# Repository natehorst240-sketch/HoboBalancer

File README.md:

# HoboBalancer

Hobby helicopter rotor-balancing instrumentation. KiCad 10 projects plus ESP32-S3
firmware.

> **Reference and troubleshooting only.** These boards report approximate RPM, 1/rev
> vibration magnitude, phase, stability and trends. Maintenance balancing remains with
> calibrated MicroVib / DynaVibe equipment. Neither the firmware nor the physical
> measurement accuracy has been validated on a bench, let alone on an aircraft. Nothing
> here is airworthiness-approved.

Open the projects in **KiCad 10.0.3 or later**. They use the KiCad 10 file format and
KiCad 9 will not open them.

## Projects

| Directory | Board | Revision | State |
|---|---|---|---|
| `.` (root) | `Balancer` — STM32 balancer | Rev A | Schematic only; `Balancer.kicad_pcb` is an empty stub |
| `BalancerREF/` | **HOBOVibe** — ESP32-S3 reference puck | **Rev G** | 50 × 50 mm, 4 layer, fully routed, DRC clean apart from three accepted warnings (see below) |
| `BalancerREF_OptHead/` | Optical tach head | **Rev B** | 25 × 50 mm, 2 layer, routed; no mounting holes yet |

Both boards are routed. On the main board `SYS`, `SYS_SW`, `BAT` and `USB_VBUS` had been
routed across In2.Cu, which is the +3V3 plane; those tracks were removed on 2026-09-18 so
the plane is whole again, and those four nets were then re-routed on the outer layers (PR #7,
merged with Rev G on 2026-09-19). The Rev G connections (U7 pass-through, R39) are routed too.
`BalancerREF/review/drc-review.rpt` (KiCad 10.0.6) shows 0 errors and 0 unconnected; what is
left is the GCT USB-C footprint's own peg-to-pad spacing (4), the ESP32 antenna overhanging
the edge by design (2) and the locally edited U1 footprint (1).
Placement was machine-generated and then adjusted by hand; look at it in pcbnew before
trusting it.

Both carry pick-and-place **fiducials** (1 mm dot, 2 mm mask opening): three per
populated face, at three of the four corners. Never four — a symmetric set gives the
placement machine no way to tell a 180°-rotated panel from a correct one. The main
board has them on both faces; the optical head is single-sided so its back has none.

### Track widths

Net classes are set in each `.kicad_pro`, sized from IPC-2221 at 1 oz outer copper and
a 10 °C rise (0.20 mm ≈ 0.74 A, 0.50 mm ≈ 1.45 A, 0.80 mm ≈ 2.03 A):

| Class | Track | Nets |
|---|---|---|
| Default | 0.20 mm | everything else |
| Power | 0.50 mm | `+3V3` `SYS` `SYS_SW` `BAT` `USB_VBUS` `GND` |
| Switch | 0.80 mm | `U6-L1` `U6-L2` — main board only |
| USB | 0.20 mm | `D+`/`D-` both sides, diff pair 0.20/0.15 |
| Emitter | 0.80 mm | `SYS_SW` `D1-A` `D1-K` — head board only |

The emitter resistor is sized at the **top** of the SYS_SW range, not at the battery.
The BQ24075 regulates OUT to 5.5 V, so R18 is 3.9 Ω for about 0.49 A at a full cell and
about 0.90 A worst case — under D1's 1 A absolute maximum. At the old 3.0 Ω the USB case
reached roughly 1.1 A.

Two caveats. **Switch clearance stays at 0.20 mm**, not the 0.25 the wider track might
suggest: the TPS63031's WSON-10 places its own L1/L2 pads 0.20 mm from its thermal
pad, so anything stricter fails inside the package and no routing choice can fix it.
And the **USB numbers are not an impedance solution** — real 90 Ω differential needs
the fab's actual stackup. The ESP32-S3's native USB is Full Speed (12 Mbps), where
that matters far less than it would at High Speed.

### BalancerREF (HOBOVibe)

The main puck. ESP32-S3-MINI-1, IIS3DWB vibration sensor on SPI, LM1815 magnetic tach
front end, BQ24075 charger with an integrated dynamic power path, TPS63031 buck-boost, and a
1x05 header for an optional u-blox-class GPS used by the in-flight logging mode.

Two measurement profiles: **MR-VERT** uses an external isolated two-wire VR pickup;
**TR-VERT** uses the optical tach against retroreflective tape.

50 × 50 mm, four layers, components on both faces: ICs, connectors, switches and test
points on the front, passives on the back so each decoupling cap sits under its IC's
power pins. M2.5 mounting holes at the four corners, on a 43.40 × 42.90 mm rectangle
centred on the board. U1's antenna deliberately overhangs the top edge, which puts
almost all of its keepout off the board — the wide band still reaches 0.44 mm inside
the top edge, which is why the mounting-hole rectangle is 0.5 mm shorter than it is
wide. The overhang is required anyway, because the aluminium bracket must not sit
behind a PCB antenna.

The puck mounts **vertically, ESP32 to the left and USB-C to the right**. `UP` and
`LEFT` markers on the front silkscreen record that; with the board vertical the
accelerometer's vertical axis is in-plane (stiff) and the flexible out-of-plane axis
carries lateral instead. Which sensor channel that is still needs recording from
DS12569's orientation figure — firmware can also identify it at runtime, since the
vertical axis reads a static 1 g when the puck is mounted upright.

Three switches: SW1 power slide, SW2 acquire, SW3 boot. There is no reset button —
SW1 feeds U6's VIN and EN, so the power slide already power-cycles the MCU. SW1 is a
Würth WS-SLTV rated 300 mA switching; steady draw through it is about 180 mA, but BLE
TX bursts and switch-on inrush exceed that briefly. That is accepted as reduced switch
life rather than designed out — see DATASHEET-VERIFICATION.md.

**Sleep is not low power.** The LM1815 draws 3.6 mA typical (6 mA max) and sits on the
always-on 3V3 rail, as do the head's op-amp and comparator, so a sleeping puck draws
milliamps and a 500 mAh cell lasts days rather than months. If flight logging ever
depends on long sleeps, the fix is a load switch on the LM1815 and the head supply.

**Power path and charging.** A BQ24075 runs the input: it charges the cell and powers
the system from the same input independently, so charge termination is correct while
the puck is running, and it will run with a defective or absent pack. R3 (3.57 k)
sets fast charge to about 249 mA — 0.5C for a 500 mAh cell — and R35 (1.6 k) sets the
resistor-programmed input limit to about 1.0 A.

Four pins go to the MCU. `CHG_EN1` (GPIO5) and `CHG_EN2` (GPIO18) select the input
current limit; `PGOOD_N` (GPIO21) and `CHG_STAT` (GPIO38) are open-drain status inputs
with 100 k pull-ups, both **active low**. Two things are easy to get wrong here:

- The datasheet's current-limit table is indexed **(EN2, EN1)**, the reverse of the
  order the pins are named in.
- Both EN pins have 285 k internal pulldowns, so the limit is USB100 — **100 mA** —
  until firmware deliberately raises it.

`PGOOD_N` is the USB-present signal. Earlier revisions tried to infer that by comparing
two ADC dividers, because a single reading of `SYS_SW` cannot answer it: SYS was fed
either from USB through a Schottky or from the cell through a PFET, and the ranges
overlap. The BQ24075 arbitrates the input itself and simply reports the answer, so
Rev E deleted the second divider (`BAT_SENSE`, R33/R34/C31) along with its 500 k ADC
source impedance and its ~2 µA standing drain on the cell.

`SUPPLY_SENSE` (`SYS_SW/2` on GPIO12) survives as the supply-voltage reading. While the
puck runs unplugged the BQ24075 connects OUT to the battery, so it reads the cell; while
charging it reads the input-derived rail instead, not the cell. It is on ADC2_CH1, the
converter shared with the radio — worth knowing, because it is now the only supply
measurement on the board.

See [`BalancerREF/README.md`](BalancerREF/README.md) for the circuit description and
[`BalancerREF/DATASHEET-VERIFICATION.md`](BalancerREF/DATASHEET-VERIFICATION.md) for
every pin mapping checked against the manufacturer tables.

### BalancerREF_OptHead

The optical tach front end, split onto its own board on 2026-09-11. It mounts at 90° to
the main PCB on the second leg of an aluminium L-bracket, on a pivot bolt so the emitter
can be aimed at the tape. The split exists because neither optical part has leads to
form — the XPEBRD-L1 is a ceramic SMD LED and the BPW34S is the surface-mount BPW34 — so
they need their own copper.

The cut is deliberately placed **after** the comparator. The cable then carries only DC
rails and digital edges; cutting at the photodiode would have put the 10 kΩ
transimpedance summing junction on a flying lead beside a wire switching 500 mA at
20 kHz.

Connected to the main board by a 7-way cable (`J5` on both). Ground is interleaved
between the two digital lines: emitter-pulse crosstalk onto `OPT_COMP` arrives inside
the synchronous gating window by definition, so the detection logic cannot reject it and
it has to be stopped at the connector.

25 × 50 mm, two layers, **every part on the front** so B.Cu can be a ground pour. Five
short signal crossings (`AMP_INV`, `OPT_AMP`, `CMP_OUT`, `OPT_COMP`, `OPT_LED_EN`) still
run on B.Cu, two of them directly under U8, and should move to the front before fab. The
board also has **no mounting or pivot hole yet**; the position depends on the bracket. A
solid back-side ground is worth more than a clean optical face: the transimpedance summing node is
the highest-impedance point in the design and sits beside a wire switching 500 mA at
20 kHz. The cost is that the baffle and the red acrylic window have to clear the
electronics.

D1 sits centred on the optical axis with PD1 18 mm directly below it. **That spacing
and the lens keepout radius are estimates** — both are constants at the top of
`scripts/build_pcb.py` and should be set from the real Ledil TINA holder before anyone
commits to them. The spacing is the one that affects performance: it sets baffle depth
and the parallax back to the tape at the 18–24 in working range.

Refill zones (`Edit → Fill All Zones`) after any edit made outside pcbnew; the scripts
here cannot drive KiCad's zone filler.

## Verification

Both boards carry a connectivity checker that compares an exported netlist against
circuit specifications written by hand — exact net membership, so an unintended short, a
bypassed series part or a reversed two-terminal part fails rather than passing quietly.

```bash
# main board
cd BalancerREF
kicad-cli sch export netlist --format kicadsexpr -o review/BalancerREF.net BalancerREF.kicad_sch
python scripts/verify_netlist.py     # PASS: 49 exact circuit nets, 293 pin endpoints

# optical head
cd ../BalancerREF_OptHead
kicad-cli sch export netlist --format kicadsexpr -o review/OptHead.net BalancerREF_OptHead.kicad_sch
python scripts/verify_head.py        # PASS: 16 exact circuit nets, 63 pin endpoints
```

Each board has its own spec. The main board's covers everything except the optical
chain and asserts that *every* pin in the netlist belongs to some named net, so a
wrong connector pinout or a missed part fails rather than passing quietly. Run these
against a freshly exported netlist — a stale `.net` will report a green that means
nothing.

Both sheets pass ERC at **0 errors and 0 warnings**. Removing a part leaves the wires
that used to reach its pins, so `BalancerREF/scripts/fix_dangling_wires.py` sweeps those:
it removes a wire only when one end touches nothing at all, never removes a wire carrying
a label (labels attach to wire bodies, so that would silently split a net - trimming the
dead tail back to the label is the fix there), and exports the netlist before and after
to prove no pin changed net. It checks its own geometry against KiCad's ERC first and
aborts if the two disagree.

Generator scripts under `scripts/` are guarded and refuse to run without
`--overwrite-hand-layout`: both sheets were laid out by hand after generation, and the
`.kicad_sch` files are the source of truth.

## Revisions

Hardware revisions are marked with git tags rather than in filenames, so the KiCad
project names stay stable across revisions. `git tag` lists them; `git checkout revD`
gets that snapshot.

| Tag | Board state |
|---|---|
| `revC` | single board, optical front end on the main PCB, no layout |
| `revD` | optical head split out; SW4 and R5 dropped; BAT sense divider added; both boards placed |
| `revE` | MCP73831 + D2 + Q3 + R27 + R31 replaced by a BQ24075; BAT sense divider removed |
| `revF` | PD1 polarity fix; R18 3.9 ohm; U9 Schmitt NAND; switcher and TIA placement |

Rev D was defined by the **battery/supply sensing change** — `BAT_SENSE` on GPIO4
alongside `SUPPLY_SENSE`, to let firmware tell USB from battery. The board split and the
two part deletions rode along in the same revision.

Rev E is the **charge-management change**, and it removed Rev D's divider again: with a
BQ24075 arbitrating the input, `PGOOD` answers "am I on USB?" directly and the
two-divider comparison had nothing left to do. Five discrete parts went with it.

Rev F is the **repo-review revision** — no new function, but a set of corrections that
had to land before any copper is routed. One of them cleans up after Rev E: removing the
USB Schottky raised `SYS_SW`, which pushed the head's emitter resistor past D1's absolute
maximum current. The others are a logic part run outside its input-transition spec and
three placement problems, the worst being a 2.4 MHz switching loop routed through vias.
Rev F is also the first revision of the optical head since it was created, so that board
moves from Rev A to **Rev B**.

Rev F also carries the one outright **functional** defect found so far: PD1 was wired
with its anode on the transimpedance summing node, which sends the signal the wrong way
through two inverting stages and leaves the comparator unable to trip at any light level.
The optical tach could never have worked. Flipping the detector fixes it without changing
anything else; `BalancerREF/DATASHEET-VERIFICATION.md` traces the chain stage by stage,
including why the connectivity checkers passed the whole time — they prove the netlist
matches the intent, not that the intent works.

Rev G is the **Reddit-review revision** (2026-09-19). Three schematic corrections on the
main board: the USB VBUS TVS (D3) was drawn forward biased, the USB data lines now pass
through the ESD array (U7) instead of hanging off it as stubs, and U9's OPT_COMP input
gets a pull-down so it does not float when the optical head is unplugged. The board
carries the new pad nets, and the USB pass-through and the new resistor are routed.

Two review items were checked and deliberately **not** changed — SW1's current rating
and U1's footprint. `BalancerREF/DATASHEET-VERIFICATION.md` records why, so they are not
re-raised at the next review.

## Not in this repo

Build output (`.pio/`, `build/`, `release/`), the firmware virtualenv, and the
point-in-time `*-backups/` and `archives/` zips are excluded — git tracks history
itself. Manufacturer datasheets in `BalancerREF/sources/` are included for reference
alongside the pin audits; `scripts/fetch_sources.py` re-fetches them from the URLs in
`sources/urls.json`.

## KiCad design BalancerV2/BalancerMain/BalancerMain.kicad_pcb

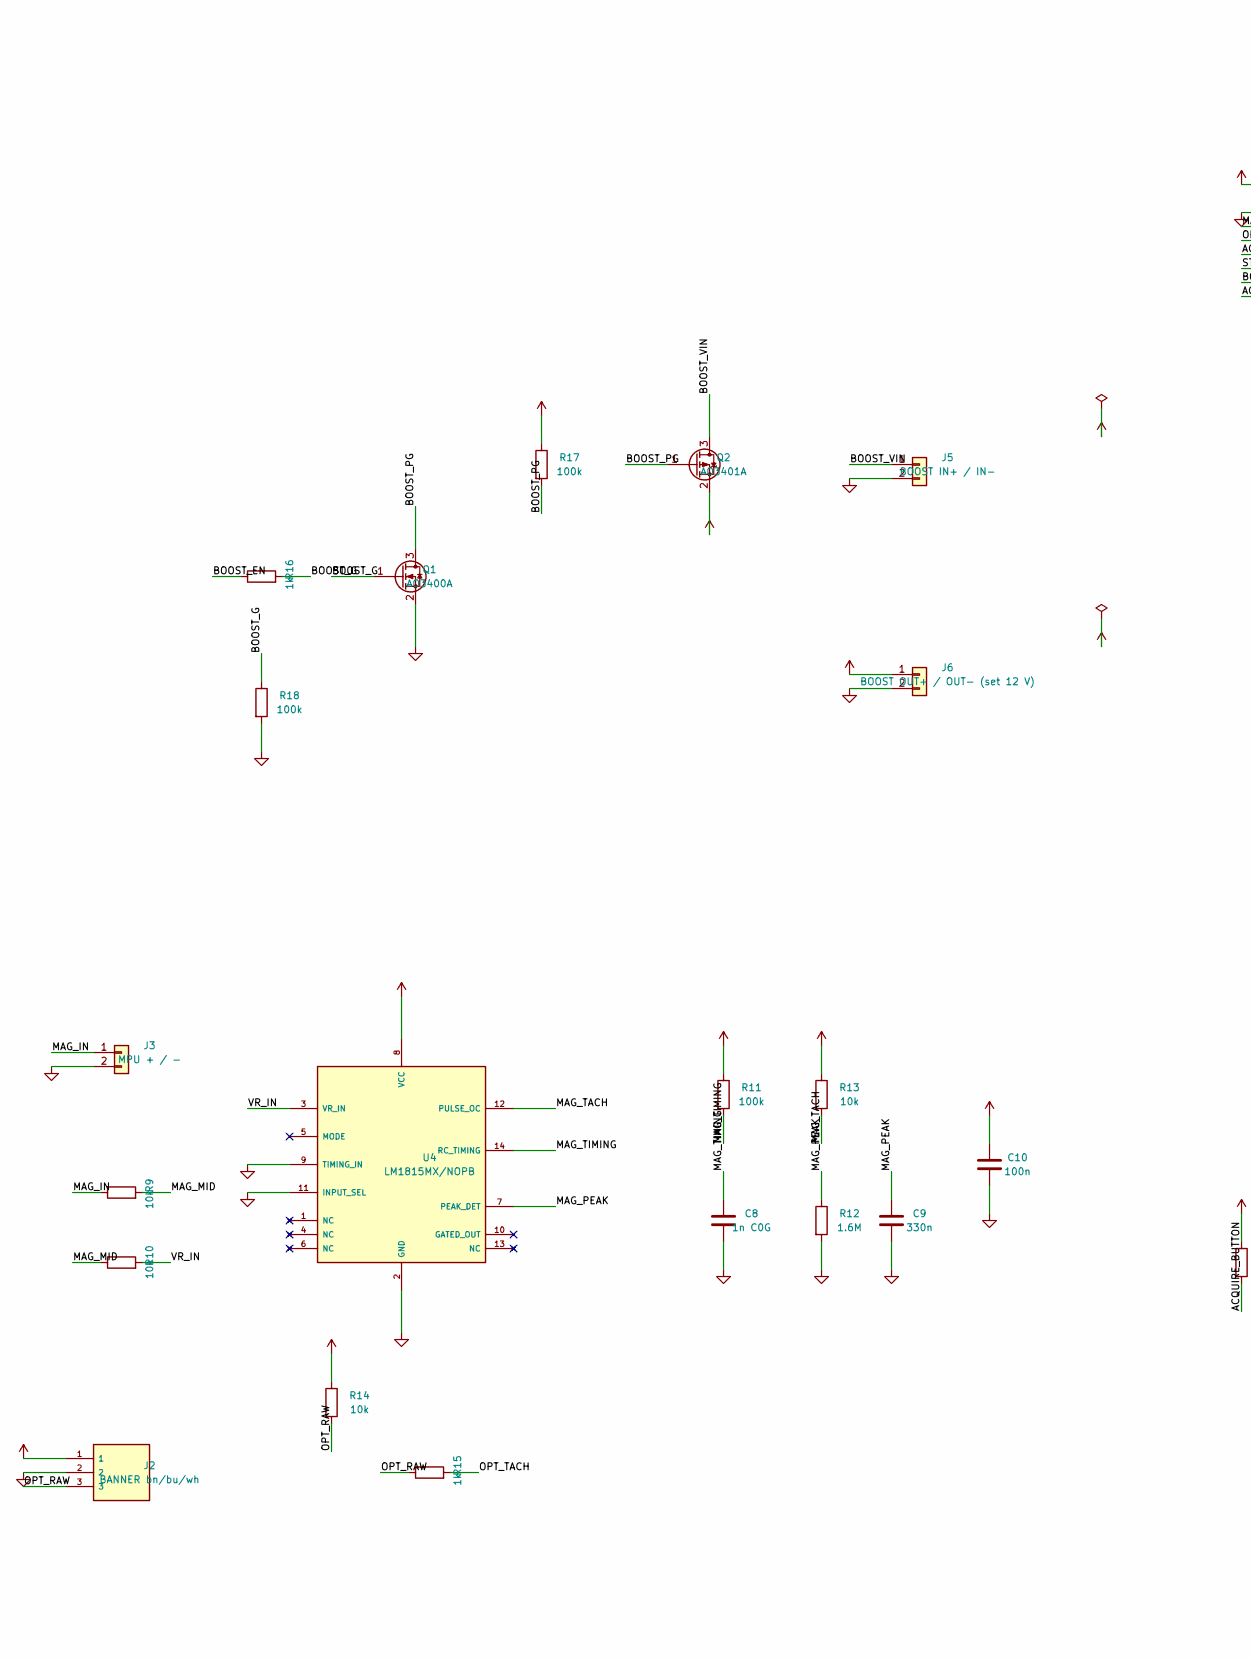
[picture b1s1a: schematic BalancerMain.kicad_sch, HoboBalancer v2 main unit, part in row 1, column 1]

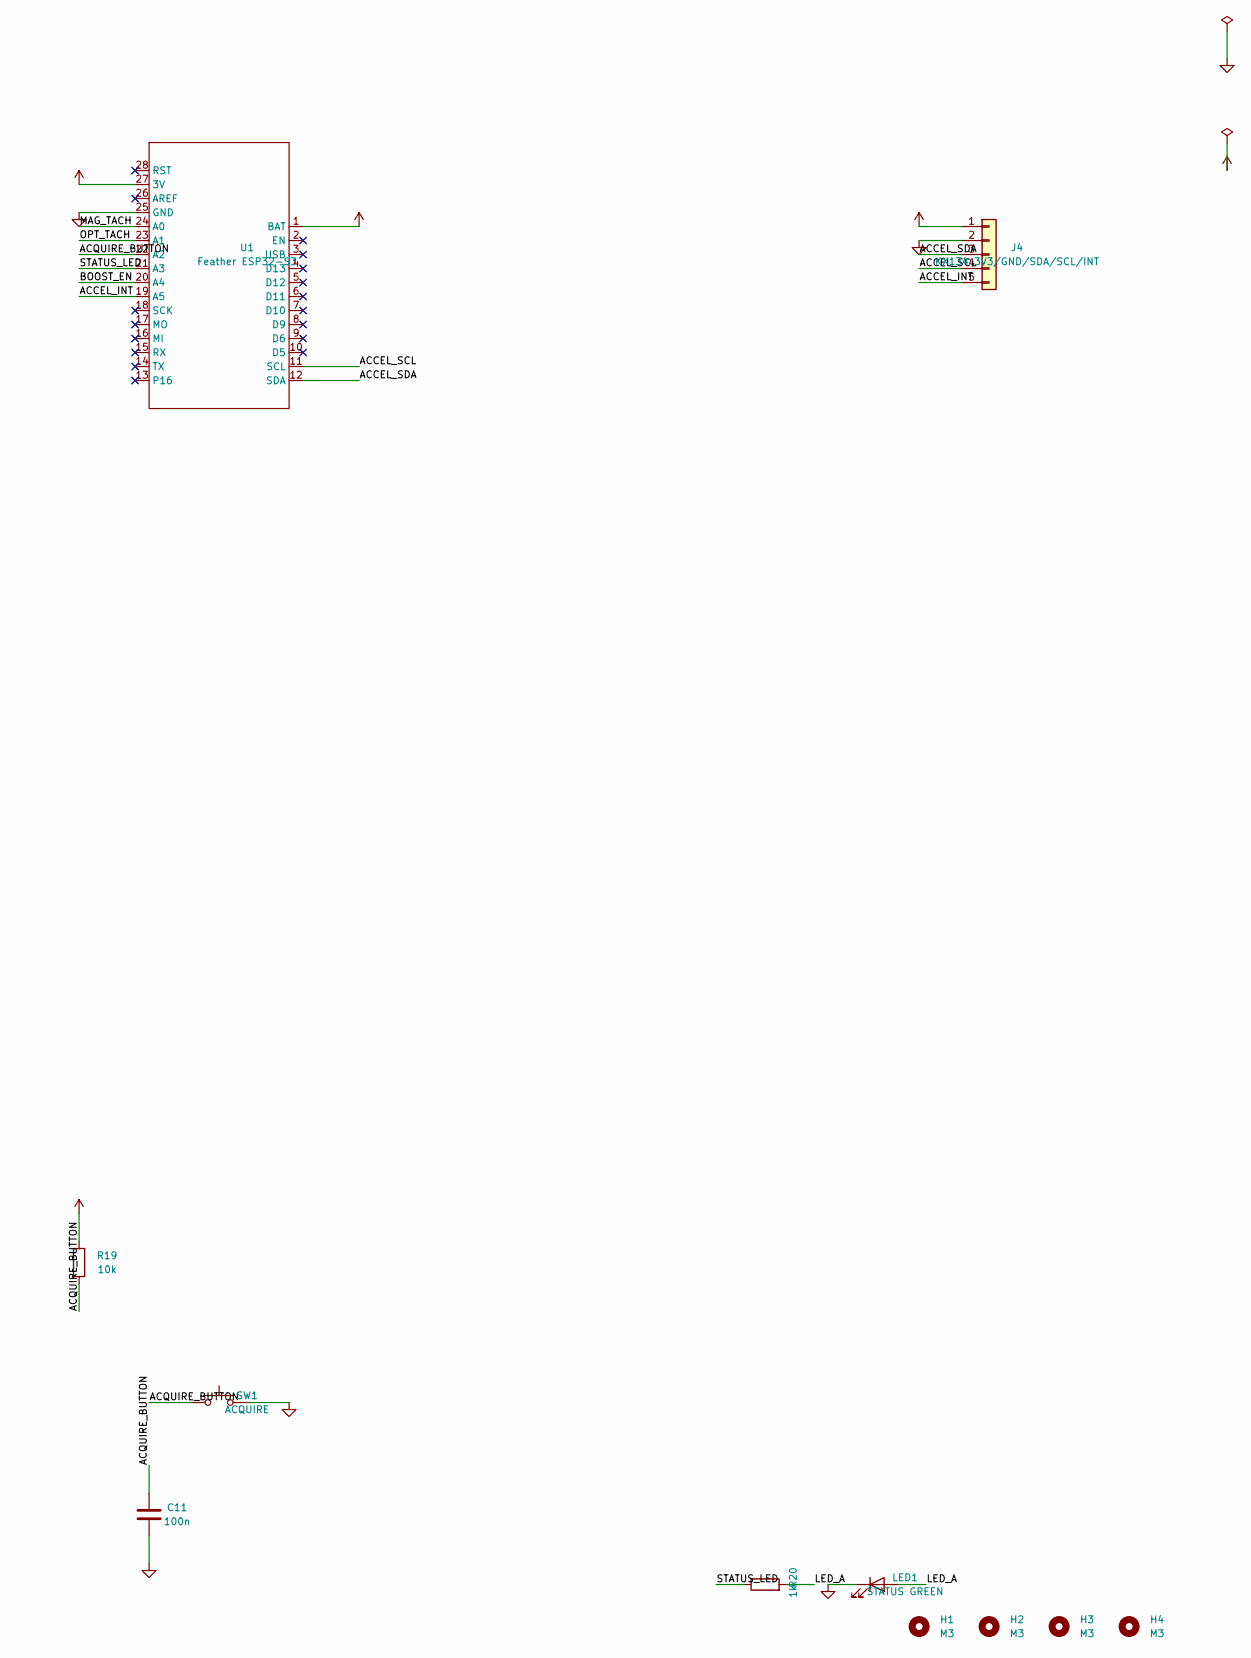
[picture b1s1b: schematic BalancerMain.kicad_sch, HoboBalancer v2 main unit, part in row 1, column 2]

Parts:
C8: 1n C0G; C_1206_3216Metric
C9: 330n; C_1206_3216Metric
C10, C11: 100n; C_1206_3216Metric
H1, H2, H3, H4: M3; MountingHole_3.2mm_M3
J2: BANNER bn/bu/wh; SolderWire_1x03
J3: MPU + / -; SolderWire_1x02
J4: KX134 3V3/GND/SDA/SCL/INT; PinHeader_1x05_P2.54mm_Vertical
J5: BOOST IN+ / IN-; SolderWire_1x02
J6: BOOST OUT+ / OUT- (set 12 V); SolderWire_1x02
LED1: STATUS GREEN; LED_0603_1608Metric
Q1: AO3400A; SOT-23
Q2: AO3401A; SOT-23
R9, R10, R13, R14, R19: 10k; R_1206_3216Metric
R11, R17, R18: 100k; R_1206_3216Metric
R12: 1.6M; R_1206_3216Metric
R15, R16, R20: 1k; R_1206_3216Metric
SW1: ACQUIRE; SW_PUSH_6mm
U1: Feather ESP32-S3; Feather_Socket
U4: LM1815MX/NOPB; SOIC-14_3.9x8.7mm_P1.27mm

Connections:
+3V3: C10.1, J4.1, R11.1, R13.1, R14.1, R19.1, U1.27 (3V), U4.8 (VCC)
+12V: J2.1, J6.1
/ACCEL_INT: J4.5, U1.19 (A5)
/ACCEL_SCL: J4.4, U1.11 (SCL)
/ACCEL_SDA: J4.3, U1.12 (SDA)
/ACQUIRE_BUTTON: C11.1, R19.2, SW1.1, U1.22 (A2)
/BOOST_EN: R16.1, U1.20 (A4)
/BOOST_G: Q1.1 (G), R16.2, R18.1
/BOOST_PG: Q1.3 (D), Q2.1 (G), R17.2
/BOOST_VIN: J5.1, Q2.3 (D)
/LED_A: LED1.2 (A), R20.2
/MAG_IN: J3.1, R9.1
/MAG_MID: R9.2, R10.1
/MAG_PEAK: C9.1, R12.1, U4.7 (PEAK_DET)
/MAG_TACH: R13.2, U1.24 (A0), U4.12 (PULSE_OC)
/MAG_TIMING: C8.1, R11.2, U4.14 (RC_TIMING)
/OPT_RAW: J2.3, R14.2, R15.1
/OPT_TACH: R15.2, U1.23 (A1)
/STATUS_LED: R20.1, U1.21 (A3)
/VR_IN: R10.2, U4.3 (VR_IN)
GND: C8.2, C9.2, C10.2, C11.2, J2.2, J3.2, J4.2, J5.2, J6.2, LED1.1 (K), Q1.2 (S), R12.2, R18.2, SW1.2, U1.25 (GND), U4.2 (GND), U4.9 (TIMING_IN), U4.11 (INPUT_SEL)
VBAT: Q2.2 (S), R17.1, U1.1 (BAT)

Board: 4 copper layers, 31 parts (0 on the bottom side), 22 nets, no tracks yet.

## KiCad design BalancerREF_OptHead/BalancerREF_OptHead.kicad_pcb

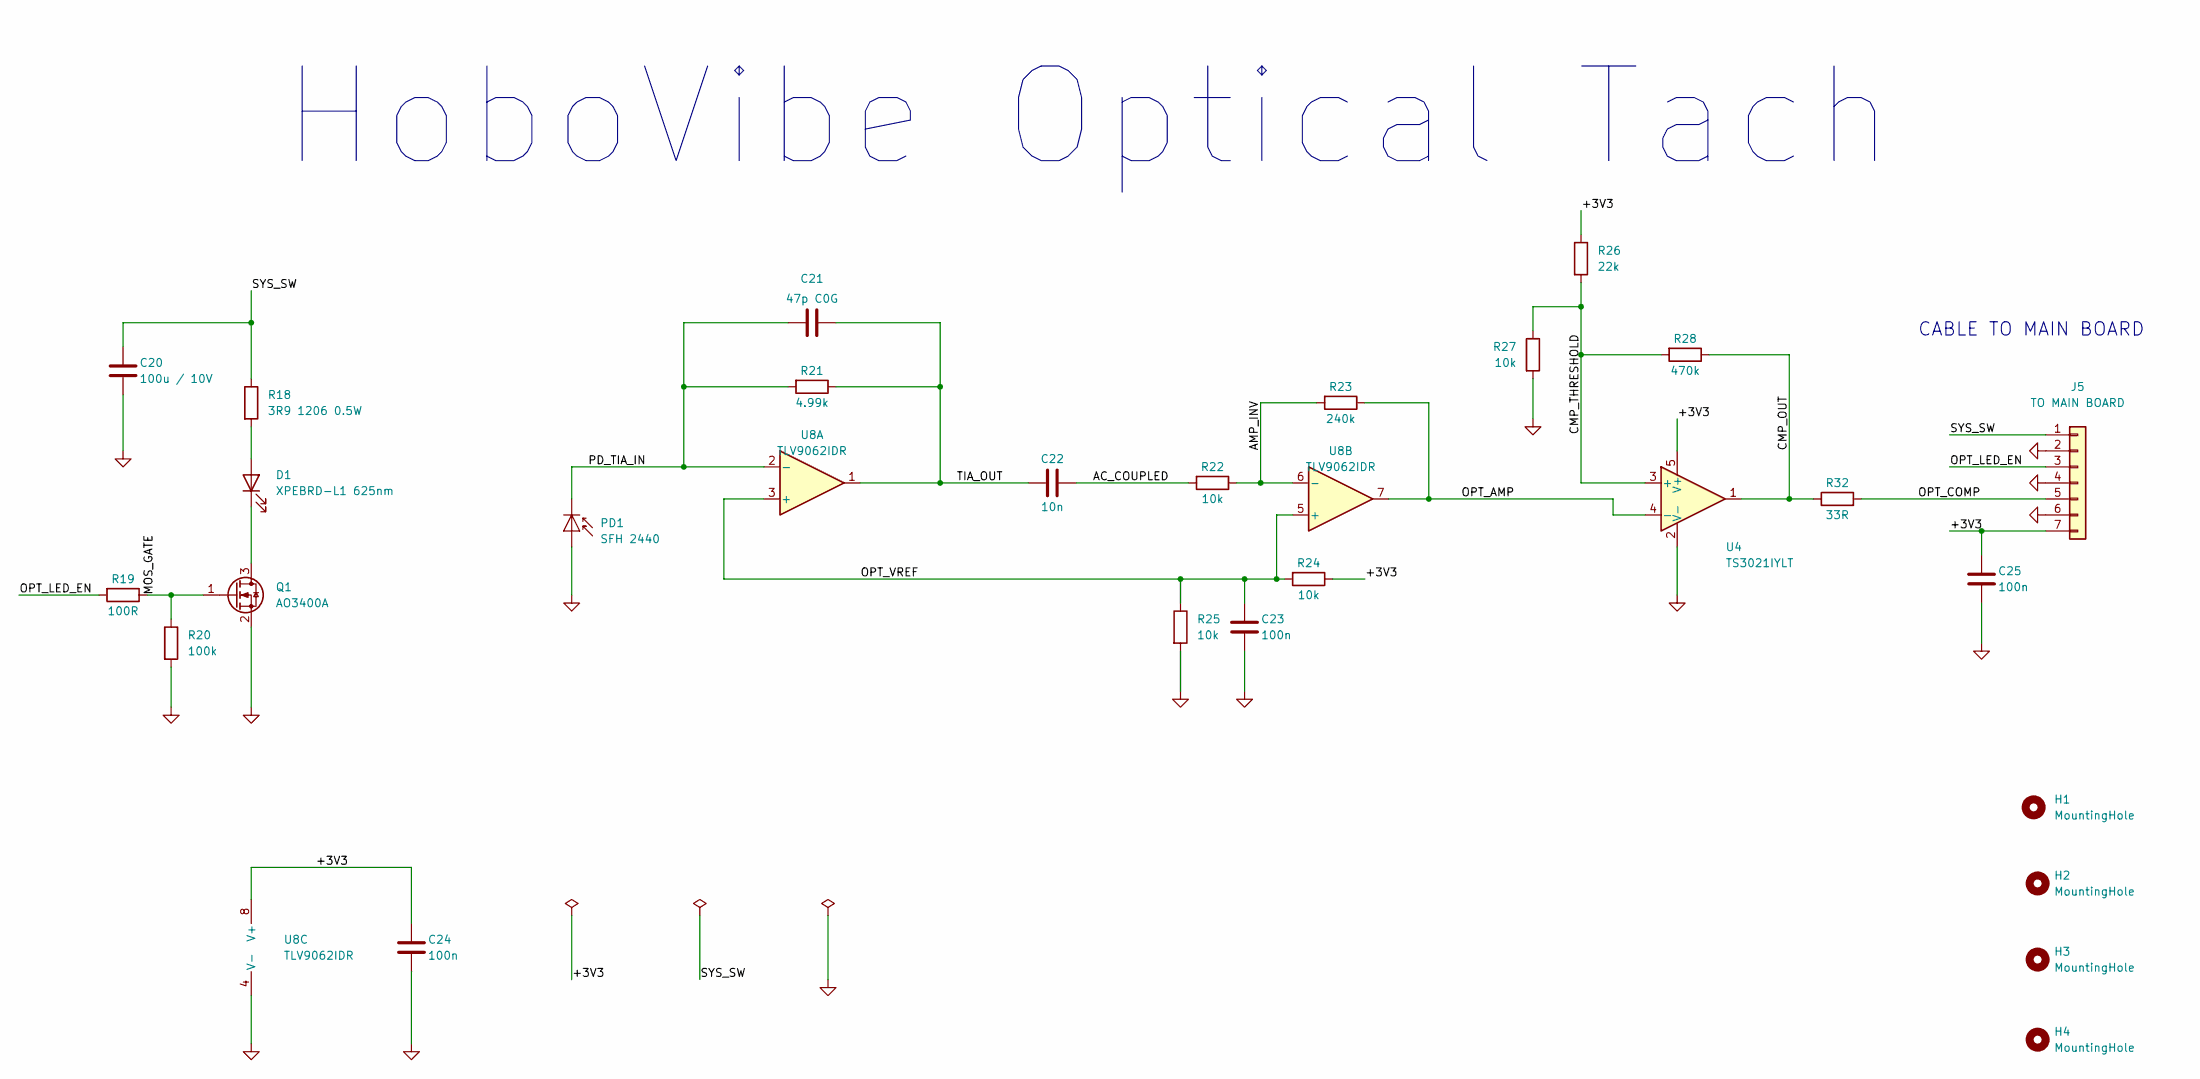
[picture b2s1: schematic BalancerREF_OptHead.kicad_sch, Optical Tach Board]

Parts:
C20: 100u / 10V; C_1210_3225Metric; MPN 100u / 10V
C21: 47p C0G; C_0805_2012Metric; MPN 47p C0G
C22: 10n; C_0805_2012Metric; MPN 10n
C23, C24, C25: 100n; C_0805_2012Metric; MPN 100n
D1: XPEBRD-L1 625nm; LED_Cree-XP; MPN XPEBRD-L1 625nm
H1, H2, H3, H4: MountingHole; MountingHole_2.2mm_M2_DIN965
J5: TO MAIN BOARD; JST_GH_SM07B-GHS-TB_1x07-1MP_P1.25mm_Horizontal; MPN TO MAIN BOARD
PD1: SFH 2440; Osram_SFH2440; MPN SFH 2440
Q1: AO3400A; SOT-23; MPN AO3400A
R18: 3R9 1206 0.5W; R_1206_3216Metric; MPN 3R9 1206 0.5W
R19: 100R; R_0603_1608Metric; MPN 100R
R20: 100k; R_0603_1608Metric; MPN 100k
R21: 4.99k; R_0603_1608Metric; MPN 4.99k
R22, R24, R25, R27: 10k; R_0603_1608Metric; MPN 10k
R23: 240k; R_0603_1608Metric; MPN 240k
R26: 22k; R_0603_1608Metric; MPN 22k
R28: 470k; R_0603_1608Metric; MPN 470k
R32: 33R; R_0603_1608Metric; MPN 33R
U4: TS3021IYLT; SOT-23-5; MPN TS3021IYLT
U8: TLV9062IDR; SOIC-8_3.9x4.9mm_P1.27mm; MPN TLV9062IDR

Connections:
/+3V3: C24.1, C25.1, J5.7, R24.1, R26.1, U4.5 (V+), U8.8 (V+)
/AC_COUPLED: C22.2, R22.2
/AMP_INV: R22.1, R23.2, U8.6 (-)
/CMP_OUT: R28.1, R32.1, U4.1
/CMP_THRESHOLD: R26.2, R27.1, R28.2, U4.3 (+)
/MOS_GATE: Q1.1 (G), R19.1, R20.1
/OPT_AMP: R23.1, U4.4 (-), U8.7
/OPT_COMP: J5.5, R32.2
/OPT_LED_EN: J5.3, R19.2
/OPT_VREF: C23.1, R24.2, R25.1, U8.3 (+), U8.5 (+)
/PD_TIA_IN: C21.1, PD1.1 (K), R21.2, U8.2 (-)
/SYS_SW: C20.1, J5.1, R18.1
/TIA_OUT: C21.2, C22.1, R21.1, U8.1
GND: C20.2, C23.2, C24.2, C25.2, J5.2, J5.4, J5.6, PD1.2 (A), Q1.2 (S), R20.2, R25.2, R27.2, U4.2 (V-), U8.4 (V-)
unnamed: D1.2 (A), R18.2
unnamed: D1.1 (K), Q1.3 (D)

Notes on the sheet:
HoboVibe Optical Tach
CABLE TO MAIN BOARD

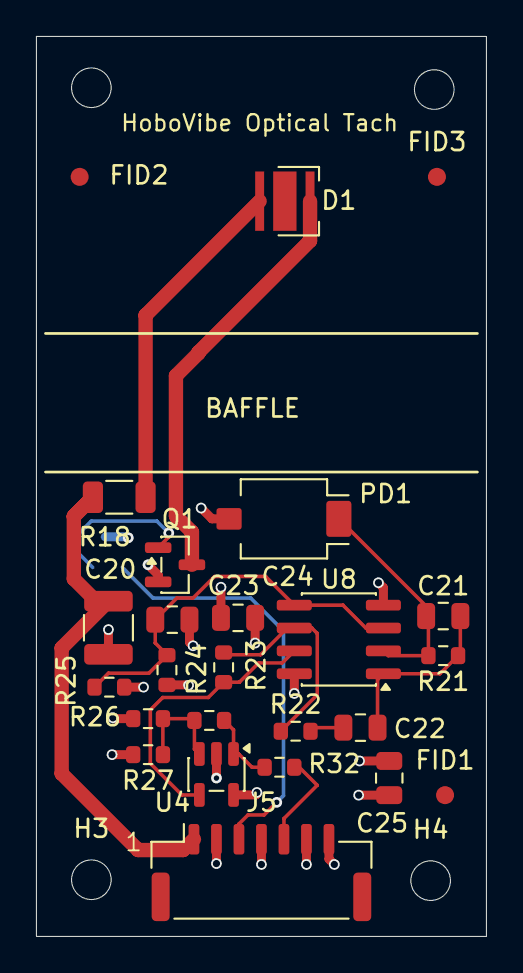
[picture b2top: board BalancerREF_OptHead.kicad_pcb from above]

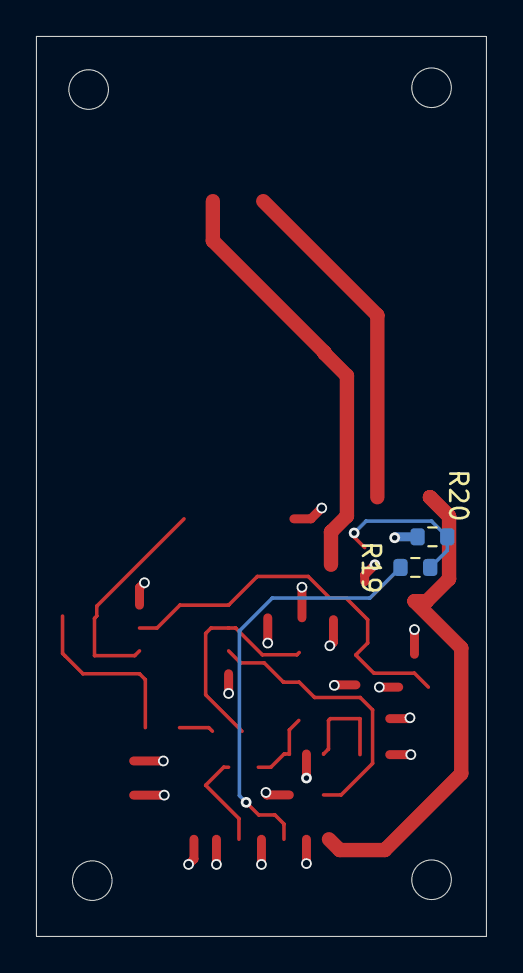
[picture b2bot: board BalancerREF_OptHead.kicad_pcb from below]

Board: 4 copper layers, 25.0 x 50.0 mm, 31 parts (2 on the bottom side), 16 nets.

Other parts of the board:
FID1, FID2, FID3: FIDUCIAL; Fiducial_1mm_Mask2mm

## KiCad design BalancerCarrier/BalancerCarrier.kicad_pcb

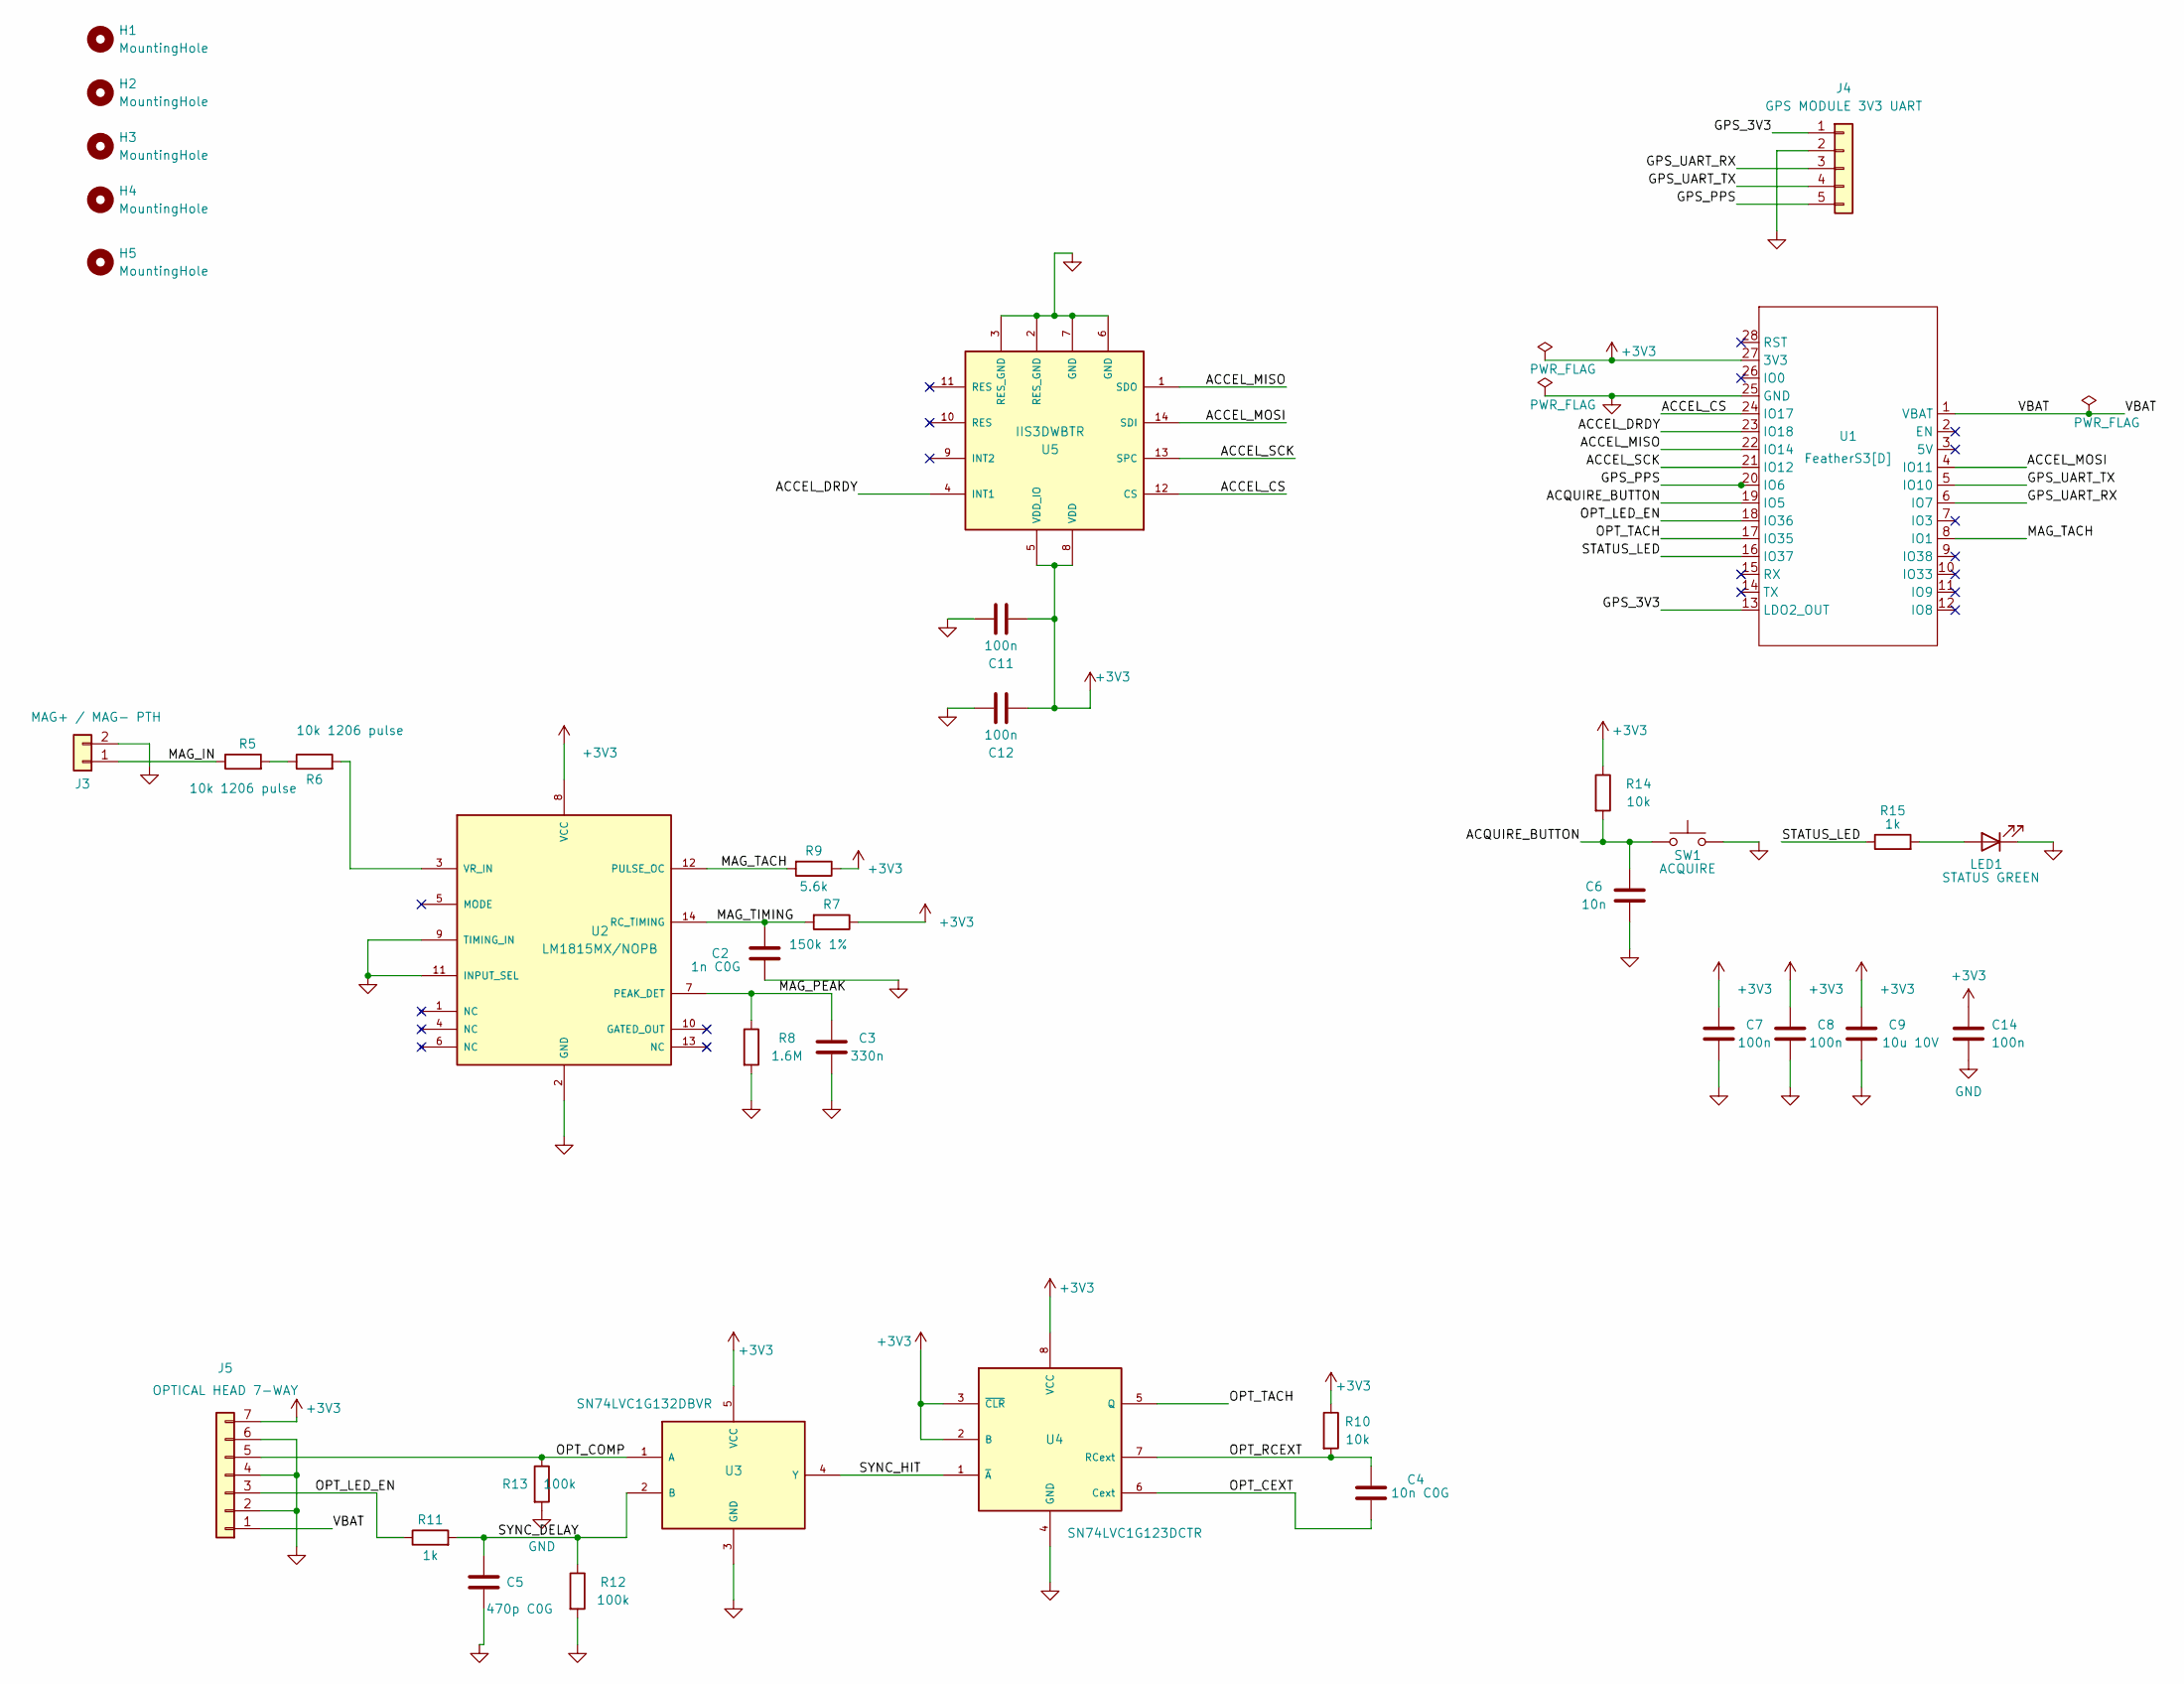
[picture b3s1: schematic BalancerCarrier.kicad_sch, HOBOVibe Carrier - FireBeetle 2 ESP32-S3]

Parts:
C2: 1n C0G; C_0805_2012Metric
C3: 330n; C_0805_2012Metric
C4: 10n C0G; C_0805_2012Metric
C5: 470p C0G; C_0805_2012Metric
C6: 10n; C_0805_2012Metric
C7, C8, C11, C12, C14: 100n; C_0805_2012Metric
C9: 10u 10V; C_0805_2012Metric
H1, H2, H3, H4, H5: MountingHole; MountingHole_2.2mm_M2
J3: MAG+ / MAG- PTH; SolderWire-0.1sqmm_1x02_P3.6mm_D0.4mm_OD1mm
J4: GPS MODULE 3V3 UART; PinHeader_1x05_P2.54mm_Vertical
J5: OPTICAL HEAD 7-WAY; JST_GH_SM07B-GHS-TB_1x07-1MP_P1.25mm_Horizontal
LED1: STATUS GREEN; LED_0603_1608Metric
R5, R6: 10k 1206 pulse; R_1206_3216Metric
R7: 150k 1%; R_0603_1608Metric
R8: 1.6M; R_0603_1608Metric
R9: 5.6k; R_0603_1608Metric
R10, R14: 10k; R_0603_1608Metric
R11, R15: 1k; R_0603_1608Metric
R12, R13: 100k; R_0603_1608Metric
SW1: ACQUIRE; SW_PUSH_6mm
U1: FeatherS3[D]; FeatherS3
U2: LM1815MX/NOPB; SOIC-14_3.9x8.7mm_P1.27mm
U3: SN74LVC1G132DBVR; SOT-23-5
U4: SN74LVC1G123DCTR; SSOP-8_2.95x2.8mm_P0.65mm
U5: IIS3DWBTR; LGA-14_3x2.5mm_P0.5mm_LayoutBorder3x4y

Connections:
+3V3: C7.1, C8.1, C9.1, C11.1, C12.1, C14.1, J5.7, R7.1, R9.1, R10.1, R14.1, U1.27 (3V3), U2.8 (VCC), U3.5 (VCC), U4.2 (B), U4.3 (~CLR), U4.8 (VCC), U5.5 (VDD_IO), U5.8 (VDD)
/ACCEL_CS: U1.24 (IO17), U5.12 (CS)
/ACCEL_DRDY: U1.23 (IO18), U5.4 (INT1)
/ACCEL_MISO: U1.22 (IO14), U5.1 (SDO)
/ACCEL_MOSI: U1.4 (IO11), U5.14 (SDI)
/ACCEL_SCK: U1.21 (IO12), U5.13 (SPC)
/ACQUIRE_BUTTON: C6.1, R14.2, SW1.1, U1.19 (IO5)
/GPS_3V3: J4.1, U1.13 (LDO2_OUT)
/GPS_PPS: J4.5, U1.20 (IO6)
/GPS_UART_RX: J4.3, U1.6 (IO7)
/GPS_UART_TX: J4.4, U1.5 (IO10)
/MAG_IN: J3.1, R5.1
/MAG_PEAK: C3.1, R8.1, U2.7 (PEAK_DET)
/MAG_TACH: R9.2, U1.8 (IO1), U2.12 (PULSE_OC)
/MAG_TIMING: C2.1, R7.2, U2.14 (RC_TIMING)
/OPT_CEXT: C4.2, U4.6 (Cext)
/OPT_COMP: J5.5, R13.1, U3.1 (A)
/OPT_LED_EN: J5.3, R11.1, U1.18 (IO36)
/OPT_RCEXT: C4.1, R10.2, U4.7 (RCext)
/OPT_TACH: U1.17 (IO35), U4.5 (Q)
/STATUS_LED: R15.1, U1.16 (IO37)
/SYNC_DELAY: C5.1, R11.2, R12.1, U3.2 (B)
/SYNC_HIT: U3.4 (Y), U4.1 (~A)
/VBAT: J5.1, U1.1 (VBAT)
GND: C2.2, C3.2, C5.2, C6.2, C7.2, C8.2, C9.2, C11.2, C12.2, C14.2, J3.2, J4.2, J5.2, J5.4, J5.6, LED1.1 (K), R8.2, R12.2, R13.2, SW1.2, U1.25 (GND), U2.2 (GND), U2.9 (TIMING_IN), U2.11 (INPUT_SEL), U3.3 (GND), U4.4 (GND), U5.2 (RES_GND), U5.3 (RES_GND), U5.6 (GND), U5.7 (GND)
unnamed: LED1.2 (A), R15.2
unnamed: R5.2, R6.1
unnamed: R6.2, U2.3 (VR_IN)

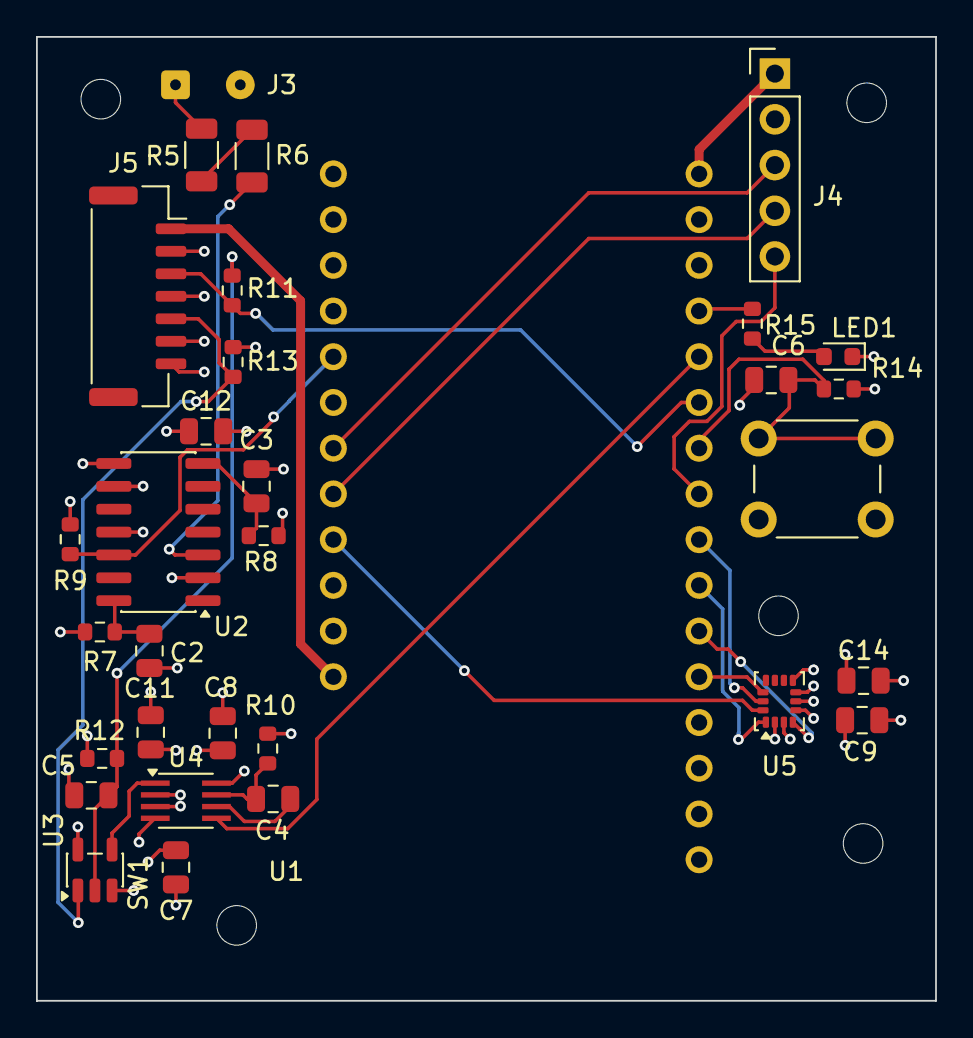
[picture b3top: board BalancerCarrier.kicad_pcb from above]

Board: 4 copper layers, 50.0 x 53.6 mm, 37 parts (0 on the bottom side), 28 nets.

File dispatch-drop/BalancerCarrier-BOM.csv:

"Refs","Qty","Value","Footprint","Datasheet","MPN","Manufacturer","LCSC","DNP"
"C2","1","1n C0G","Capacitor_SMD:C_0805_2012Metric","","","","",""
"C3","1","330n","Capacitor_SMD:C_0805_2012Metric","","","","",""
"C4","1","10n C0G","Capacitor_SMD:C_0805_2012Metric","","","","",""
"C5","1","470p C0G","Capacitor_SMD:C_0805_2012Metric","","","","",""
"C6","1","10n","Capacitor_SMD:C_0805_2012Metric","","","","",""
"C7,C8,C11,C12,C14","5","100n","Capacitor_SMD:C_0805_2012Metric","","","","",""
"C9","1","10u 10V","Capacitor_SMD:C_0805_2012Metric","","","","",""
"J4","1","GPS MODULE 3V3 UART","Connector_PinHeader_2.54mm:PinHeader_1x05_P2.54mm_Vertical","","","","",""
"J5","1","OPTICAL HEAD 7-WAY","Connector_JST:JST_GH_SM07B-GHS-TB_1x07-1MP_P1.25mm_Horizontal","","","","",""
"LED1","1","STATUS GREEN","LED_SMD:LED_0603_1608Metric","","","","",""
"R5,R6","2","10k 1206 pulse","Resistor_SMD:R_1206_3216Metric","","","","",""
"R7","1","150k 1%","Resistor_SMD:R_0603_1608Metric","","","","",""
"R8","1","1.6M","Resistor_SMD:R_0603_1608Metric","","","","",""
"R9","1","5.6k","Resistor_SMD:R_0603_1608Metric","","","","",""
"R10,R14","2","10k","Resistor_SMD:R_0603_1608Metric","","","","",""
"R11,R15","2","1k","Resistor_SMD:R_0603_1608Metric","","","","",""
"R12,R13","2","100k","Resistor_SMD:R_0603_1608Metric","","","","",""
"SW1","1","ACQUIRE","Button_Switch_THT:SW_PUSH_6mm","","","","",""
"U1","1","FeatherS3[D]","BalancerCarrier:FeatherS3","","","","",""
"U2","1","LM1815MX/NOPB","Package_SO:SOIC-14_3.9x8.7mm_P1.27mm","","","","",""
"U3","1","SN74LVC1G132DBVR","Package_TO_SOT_SMD:SOT-23-5","","","","",""
"U4","1","SN74LVC1G123DCTR","Package_SO:SSOP-8_2.95x2.8mm_P0.65mm","","","","",""
"U5","1","IIS3DWBTR","Package_LGA:LGA-14_3x2.5mm_P0.5mm_LayoutBorder3x4y","","","","",""
